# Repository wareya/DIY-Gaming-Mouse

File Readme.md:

# DIY Gaming Mouse

Video about why and how I made this, and what the various iterations were like: https://www.youtube.com/watch?v=h-Cdl4Vq9H4

This repository contains the code, schematic, PCB layout, and 3d model for a completely DIY gaming mouse, all designed around a Pixart PMW3360 sensor.

The firmware for this mouse uses a special debouncing algorithm that completely eliminates chatter without adding ANY latency, and eliminates bounce better than commercial mice do. Random double-clicks be gone!

None of the companies that make gaming mouse sensors sell them to consumers, including Pixart, so the sensor needs to be salvaged (or bought from a scalper, or a small business that specializes in reselling them).

<table>
  <tr>
    <td>
      
    </td>
    <td>
      
    </td>
  </tr>
  <tr>
    <td>
      opened mouse
    </td>
    <td>
      assembled mouse
    </td>
  </tr>
</table>

(The shell has a top, too, but it's turned off in this picture so you can see the PCB.)

## Features

- True zero-latency button debouncing with no glitching
- Buttons that will not develop double-clicking problems after only a few months
- Low-latency motion tracking (no smoothing)
- Completely open source (Apache 2.0 license)
- Even the hardware is open source! (except the processor and sensor)
- Ultra light-weight shell and assembly (55g in total)
- Fingertip-grip shell shape
- Extra middle mouse button
- - the button that normally controls DPI on other mice is mapped to M3
- PCB exposes extra unused pins from the rp2040 as test pads for hardware/firmware modding fun; attach your own sensors! or LEDs! whatever you want!
- Full 1000hz tracking

TODO:

- Configurable DPI (currently hardcoded at 1200)
- - To change it in the firmware code, edit the `spi_write(REG_CONFIG1, 11); // 1200 dpi` line, replacing 11 with your dpi divided by 100 minus 1, e.g. 7 for 800 dpi, 3 for 400, 15 for 1600, etc
- rebinding, macros, etc
- - can already be hardcoded atm if you're skilled at programming
- "fun" optional features like WMO-style diagonal jaggy removal or optional in-firmware acceleration, anti-smoothing (prediction), angle snapping, cinematic smoothing, etc
- [Wireless](https://github.com/wareya/DIY-Gaming-Mouse/issues/8)

## Required skills

You need to be familiar with, or be able to learn quickly:

- 3d printing
- how to use a "slicer" (e.g. Cura) to convert stl models to gcode (what your 3d printer uses)
- repeatedly making test prints
- how to clean up 3d prints and remove support material from fragile prints
- basic firmware code debugging skills
- the ability to read embedded C/C++ code
- the Arduino IDE (I use 2.x, not 1.x)
- desoldering (with a hot air rework station)
- soldering (with a soldering iron)
- soldering bodge wires to existing pieces of hardware without creating solder bridges (for SROM extraction)
- comfort using a hot air rework station to soften and fix misshapen parts on 3d printed objects if they print improperly
- the ability to do all of the above without wasting tons of money or burning your home down
- familiarity with PCB printing companies and PCB assembly manufacturers (JLCPCB, PCBWay, etc)
- patience

If you cannot do all of the above, you should have someone else build this project for you, rather than building it for yourself. Or, at the very least, I can't give you support if you don't have the skills needed to make this; I'm just some random guy.

You also need:

- access to a 3d printer that you can repeatedly print test prints on until they come out right
- a hot air rework station with temperature and air flow rate control
- a soldering iron with temperature control
- hot glue device (for securing the USB cable, nothing else)
- various small tools like screwdrivers, tweezers, cleanup blades / deburring tools, etc. for various parts of the building process

## Instructions

### 3D printing the shell

This assumes you're using a filament printer. Resin printers might work too, but I have never used one.

I print with PLA filament.

Print each of the STL files in the "Case Model" directory in their natural (not default!) orientations. To repeat, some of the models have to be rotated; they're saved in the orientation they have in the mouse, not the orientation they need to have on the 3d printer's build plate.

You need to convert the stl files to gcode yourself and run various test prints because each 3d printer and filament has different requirements for layer thickness, support cutoff angle, printing speed, z seam alignment placement, etc.

Cura will complain about certain pieces (like the shell bottom) not being "water tight", but it's wrong; the watertightness check doesn't handle multiple overlapping solids properly. The models will still slice correctly and without glitches.

The thumb pieces must be rotated into the orientation where they do not need any supports. This means the small part of the thumb piece is facing up, and the long part of the switch clamp section is on the bottom.

The scroll wheel must be rotated so that the thick cylinder part is on the bottom and the thin pin part is on the top. It must be printed with supports; any type of support is fine. It should be printed at 100% speed or lower, not higher, until it gets to the pin, at which point you MUST reduce the printing speed as low as you can tolerate. On my printer, a Sovol SV06, I had to turn it down to 25% speed. If your printer doesn't allow you to change the speed mid-print, you have to print at the low speed for the entire print. This is important; you have to print it slowly, because otherwise, the pin will be misaligned with itself and the scroll wheel will be off-balance and hit the middle mouse button switch with different pressures depending on where it is in its spin cycle.

Print the scroll wheel brace as-is.

Print the shell bottom as-is. However, if you have a heated printbed or chamber, you need to wait for it to completely cool before removing it. If you remove the print while it's warm, the bottom will bend and the mouse won't sit flat. Even with mouse feet, the sensor will be at the wrong height if the bottom is bent.

Print the shell top with tree supports and a support cutoff angle between 60 and 70 degrees. Do not use "standard"/traditional/grid supports; they will be too difficult to remove, and you will probably damage the print trying to remove them. On my printer, a Sovol SV06, 67 degrees was just right. If you have poor print quality, you might need to reduce the cutoff angle down to something silly like 50 degrees. If you have to go below 50 degrees, get a better printer, or make sure you're using the right filament at the right temperature, etc.

Once the shell top is printed, you need to use a deburring tool (or other hard, sharp metal implement) to remove a small amount of material from a certain curved edge along the seam where it meets the shell bottom, on the right side of the shell (with the button pieces away from you and the "butt" part towards you). The shell will fit together without removing a small amount of material from this part of the shell top, but it'll be misaligned by around a quarter of a millimeter and the right click won't quite work right. This material has to be removed because it sags during printing, and it sags during printing because of how support bridging works; the 3d model itself is correct.

You should print each part one-by-one and check for errors each time.

The final result will be somewhat rough and rugged, but it's a functional mouse shell.

### SROM preparation

Note: The SROM is optional, but highly recommended because it contains sensor firmware bugfixes. If you can't get it, comment out the call to `srom_upload();` in `pmw3360_boot()`, and then rename the `.h` file inclusion to `#include "srom_dummy_blank.h"`, but be warned that your mouse might experience glitchy behavior like "spinout" or have generally poor tracking. For example, while writing this and testing the firmware without an SROM, I click-and-dragged a title bar on a window, and then the mouse cursor teleported 300~400 pixels to the right for no reason.

The SROM needs to be captured from an existing mouse because it's copyrighted. Give it the name `srom_3360_0x03.h`, `srom_3360_0x04.h`, or `srom_3360_0x05.h`, depending on what version it is. I poked around github and found other projects using the 3360 SROM, and this seems to be the way they decided to name their SROM header files, so I'm copying the filename from them.

Once you have the SROM, edit the `#include "srom_3360_0x05.h"` line in `3360_Mouse_pico.ino` to point to the file for your SROM.

The below is instructions on how to capture the SROM from a commercial mouse.

Capture the SROM from a commercial 3360 mouse with this code, and a standalone raspberry pi pico (not this mouse's custom PCB): https://gist.github.com/wareya/0dc3498bd80be93c47b6f79aa9164321

Note: the above SROM capturing code requires you to use the "arduino-pico" board type in the Arduino IDE. But the firmware in this repostory requires you to use the "mbed OS" rp2040 board type.

Use a breadboard to make a ripping setup equivalent to that depicted in the following image:

And this post: https://github.com/wareya/DIY-Gaming-Mouse/issues/6#issuecomment-2340009477

Be very careful not to create any solder bridges between any of the pins on the 3360.

Reconnect the mouse so that it reboots and sends the SROM to the sensor again.

The output should be exactly 4094 bytes long, and the second byte should be 0x03, 0x04, or 0x05 (different versions).

Repeat the capturing process until you get the same SROM several times, just to make sure that it captured properly. To capture the SROM again, you need to reboot the mouse. This can be plugging it in to your computer again, or disconnecting and reconnecting its USB power wire, or any safe method you prefer.

The MD5 checksums of the versions of the SROM that I know about are:

```
0x03 - C64F2BDA742DD1623D6A5DC869FC5E60
0x04 - 0BCB410858FF21D091DDC497D19BC943
0x05 - 337254C54AD82C689D4B9A58D06A3CF6
```

If you have an SROM with a different version number, it might not work with this firmware. It might, but it also might not. I can't provide support for other SROM versions.

After capturing the SROM data, save it in a formatted .h file formatted as such:

```c

#define SROM_LENGTH (4094)

const uint8_t PROGMEM srom[SROM_LENGTH] =
{
0x01,
0x<version number>,
// ...
// etc
};
```

I cannot distribute the SROM in this repository, because it's copyrighted proprietary code.

Disclaimer: The above steps do not bypass any copy protection, no encryption is being broken, and copyright law is not being violated by making your own backup copy of the sensor's SROM and using it on your own device. This is fully legal in reasonable countries (like the US).

### PMW 3360 sensor salvage

The Pixart PMW3360 is not sold commercially to hobbyists or small repair shops; to get one, you have to either buy an expensive breakout board, buy it from scalpers on aliexpress (or similar), or salvage it from an existing commercial mouse. This project assumes that you're salvaging it from an existing commercial mouse, after capturing the SROM from that mouse.

You need a hot air rework station, NOT a soldering iron, to desolder and salvage the 3360 safely. If you try to use a soldering iron, even with desoldering wick and/or a desoldering pump, you are VERY likely to fail to salvage it, damaging the pins or sensor internals in the process. The 3360 is somewhat sensitive to high temperatures, so you can only heat it up for a fairly short amount of time, and desoldering the ground pin with a soldering iron will get the sensor hot enough that it might start to damage it.

The 3360 sensor's lens is usually directly mounted to the sensor by melting its clear mounting pins down onto the top of the sensor's IC package.

Take the commercial mouse's PCB, scrape off (don't break off) the top melted part of the lens's mounting posts. Then, being careful not to damage anything, remove the lens from the sensor and PCB and put it somewhere safe.

Now, put the commercial mouse's PCB upside down on a non-flammable surface, in a workspace free of any flammable material. I cannot be held responsible if you start a fire in an unsafe workspace. You have been warned!

Before continuing, you might want to cover the bottom of the sensor with paper and/or tape to prevent anything from getting inside of it. If you do this, do it in a way that doesn't create a fire hazard.

Find the bottom of the sensor's pins. To each of these pins, apply a small amount of either leaded solder (if it's all you have) or low-temperature non-leaded solder paste/gel/etc (preferred) (NOT the same thing as flux!). You want to mix your solder into the existing solder on the pins because this will lower the melting temperature of the existing solder and make it easier to desolder the chip. Use a soldering iron or hot air tool at around 600F/300C to make the two types of solder mix together. Do not physically touch the PCB or pins with the hot air tool; rely only on the air itself.

Once the solder for each pin is mixed together, pass the hot air tool over each section of pins in a circular motion until the sensor eventually, finally comes loose. At this point, use any metal tool (like metal tweezers or a screw driver) to make sure the sensor fully comes out of the PCB.

Now, use a soldering iron to clean any excess remaining solder off of the pins. If the soldering iron ends up with too much solder on it, clean it off with brass/bronze wool or similar. Be warned that, at very high temperatures, brass wool is flammable. Do not use steel wool as a subtitute, as it is even more flammable.

### PCB building and assembly

Build gerber files and drill files and all the other necessary files (BOM, pick and place, etc) that your PCB manufacturer needs to print **and assemble** the PCB. Some of the components on the PCB are very, very delicate, so unless you're a genuine expert, trying to hand-solder them is doomed.

The plugin I use to manage JLCPCB part mappings is https://github.com/Bouni/kicad-jlcpcb-tools - this is the plugin that uses the `project.db` file. However, this file is just an sqlite database, so if you want to make sure you use the right parts with another manufacturer, you can open it up with any sqlite database viewer and get the LCSC part numbers and look them up individually, then find the equivalent part for your PCBA manufacturer. However, the PCB isn't designed to require you to do this; you can look up the parts individually instead (based on their values).

Once you have your PCBs, you need the following parts to manually solder to the board:

- 6 Omron D2F-01F switches (or compatible, e.g. D2FC)
- 11mm Alps-compatible scroll wheel encoder
- salvaged PMW 3360 sensor, undamaged, pins not bent
- - 3360 sensor's lens, with mounting posts still intact
- Four dupont-compatible header pins for connecting to USB cable (optional)
- spare discrete resistors in case you messed up any of the resistor values when ordering the PCB like I did

And the following additional parts for assembly:

- USB cable, ideally with dupont-compatible connectors (you can crimp them on yourself, you don't have to buy a special cable for this)
- 3d printed shell (2 parts)
- 3d printed side buttons (2 parts)
- 3d printed scroll wheel brace (1 part)
- 3d printed scroll wheel OR salvaged scroll wheel for 11mm Alps-compatible scroll wheel encoder with the right middle-mouse-button shaft thickness
- mouse feet (salvaged or custom) with approximately 0.6mm thickness (that's zero-point-six millimeters)

The mouse feet thickness is very important, within a quarter of a millimeter! Using any other thickness of mouse feet is likely to result in poor, glitchy tracking. The PMW3360 is VERY sensitive to VERY small changes in tracking distance.

Make sure you have screws the right size to screw everything together. I recommend doing a test-fit of the shell and plain PCB with screws before doing anything else. Be careful not to overtighten the side screws; doing so can cause their mounting holes to split. The PCB is held down with two screws and the case is held together with three screws. I used salvaged screws with a major diameter (outside edge of threads) of 2mm and a minor diameter of around 1.65~1.7mm, and the holes on the case were designed around these screws, but slightly different screws will still work.

Solder the dupont-compatible header pins to the PCB, or if you have a different plan to connect the PCB to USB, do that instead. Then, connect it to your computer and make sure you can program it with the Arduino IDE. If it doesn't work, try a different copy of the PCB. Don't continue until you know that the PCB and its rp2040 processor are working properly. You should also do a test-fit of the PCB inside the 3d printed shell bottom to make sure nothing went wrong in 3d printing, and that the edge cuts and drill holes on the PCB are accurate to how they were specified in the design files.

Solder each Omron switch to the board with the plungers aligned with the outline on the silkscreen illustration. Check and double check that the switches are fully flush with the board before and while you solder them; double check that they're flush after soldering the first pin.

Test fit the PCB into the shell bottom, and without screwing anything into anything else, attach the top half of the shell and make sure that the buttons can be clicked properly and aren't clicked just by attaching the top half of the shell. If they're hard to click or they click themselves, your 3d printer has poor tolerances, and you may need to adjust the button pieces by softening them with the hot air tool and bending them slightly until they fit just right. Once you're done here, remove the PCB from the shell.

Solder the scroll wheel encoder in into the RotaryEncoder footprint on the PCB. Be very sure that it's all the way down before and while soldering it. You may need to twist the pins very slightly with a pair of needle-nose pliers to get them to fit into their holes; the holes are very narrow, on purpose, to reduce the chance of solder bridges forming between them.

(Example photo of a 11mm Alps-compatible encoder. 11mm is the distance between the center of the rotor and the surface of the PCB, not the top to bottom of the entire encoder.)

Solder the PMW3360 sensor to the center of the PCB, making VERY, VERY sure that it's in ALL THE WAY before and while soldering it. If it's not in all the way, the PCB may not fit properly in the shell, and/or the sensor may fail to track properly. The sensor must be mounted "upside-down" relative to the rest of the board, such that the text on it is upside-down compared to the text at the top of the board. If you put the sensor in the wrong way, it will look uncentered; if you put it in the right way (upside-down), it will look centered. If you get the wrong, the sensor might fry itself when you turn the mouse on, and the lens might not even fit against the sensor through the PCB.

Attach the lens to the sensor on the underside of the PCB. Then, slot the PCB into the bottom shell and make sure it fully fits all the way down.

If, at this point, you connect the mouse to USB again and check what it says in the Arduino IDE's "Serial Logger" when the mouse boots, and the SROM's ID is a value other than zero or 0xFF, the sensor is working properly. If it's working properly but still doesn't track, double check the value of the LED resistor; that's the component closest to the "U10" silkscreen text, also near four diodes arranged in a rectangle (not in a row). The resistor value should be 39 ohms, or something very close like 40. If the resistor value is wrong, you have to desolder it and bodge on 40 ohms worth of discrete resistors (I personally use two 20 ohm resistors in series). WARNING: Using too few ohms will permanently damage the sensor's LED and make the sensor useless.

Remove the PCB and fit the side button thumb pieces to their switches. This is difficult and should feel like you're almost going to break the thumb pieces, but not like you're definitely going to break them. The long piece of the switch brace should wrap around the "inside" of the switches (towards the other side button switch), not the "outside". To get the thumb pieces around the switches, first fit the "hook" to the bottom around the edge of the PCB, slightly offset from the switch, and rotate the thumb piece down so that the far end of its brace hits the top of the switch. Move it as far from the switch as you comfortably can, so that it doesn't have to bend too much to slide down past the top and around the other side of the switch. Once that happens, slide it towards the switch so that the small hook piece at the end of the brace fully wraps around the other corner of the switch. Repeat this for the other switch's thumb piece.

Above is a visual image series depicting the process for mounting the thumb button pieces. It's OK if they crack or break while attempting to fit them; they will still fit and work, just be slightly less snug than they're supposed to be.

Fit scroll wheel brace around the middle mouse button (near the right mouse button), with the spikes towards the "inside" of the mouse and away from the middle mouse button. Now fit the scroll wheel and make sure it's snug and properly balanced. If it's not, you'll need to reprint it.

Put the PCB back into the shell bottom and make sure it's still snug. Route the USB cable behind the support post in the back of the case (it has a screw hole in it) and around the right side of the PCB (NOT the left side), hugging the right side of the right mouse button, and then feed it out through the slot in the front. Use hot glue to secure the USB cable to that front slot. Make sure that it points relatively straight out the front when you hot glue it down.

Plug it in, compile and upload the firmware from the Arduino IDE, and make sure everything works. If it does, you're done! Just re-screw everything together. Be careful not to overtighten the side screws; doing so can cause their mounting holes to split.

## License

3360_Mouse_pico.ino, the main file of this project, is released under the Apache License, version 2.0.

relmouse_16.h is based on files from mbed OS, also licensed under the Apache License, version 2.0. https://github.com/arduino/ArduinoCore-mbed

The hardware design files (under "Case Model" and "KiCad schematic + PCB") are licensed under the SolderpadLicense, version 2.1, as follows:

```
Copyright 2024 wareya
SPDX-License-Identifier: Apache-2.0 WITH SHL-2.1

Licensed under the Solderpad Hardware License v 2.1 (the “License”); you may not use this file except in compliance with the License, or, at your option, the Apache License version 2.0. You may obtain a copy of the License at

https://solderpad.org/licenses/SHL-2.1/

Unless required by applicable law or agreed to in writing, any work distributed under the License is distributed on an “AS IS” BASIS, WITHOUT WARRANTIES OR CONDITIONS OF ANY KIND, either express or implied. See the License for the specific language governing permissions and limitations under the License.
```

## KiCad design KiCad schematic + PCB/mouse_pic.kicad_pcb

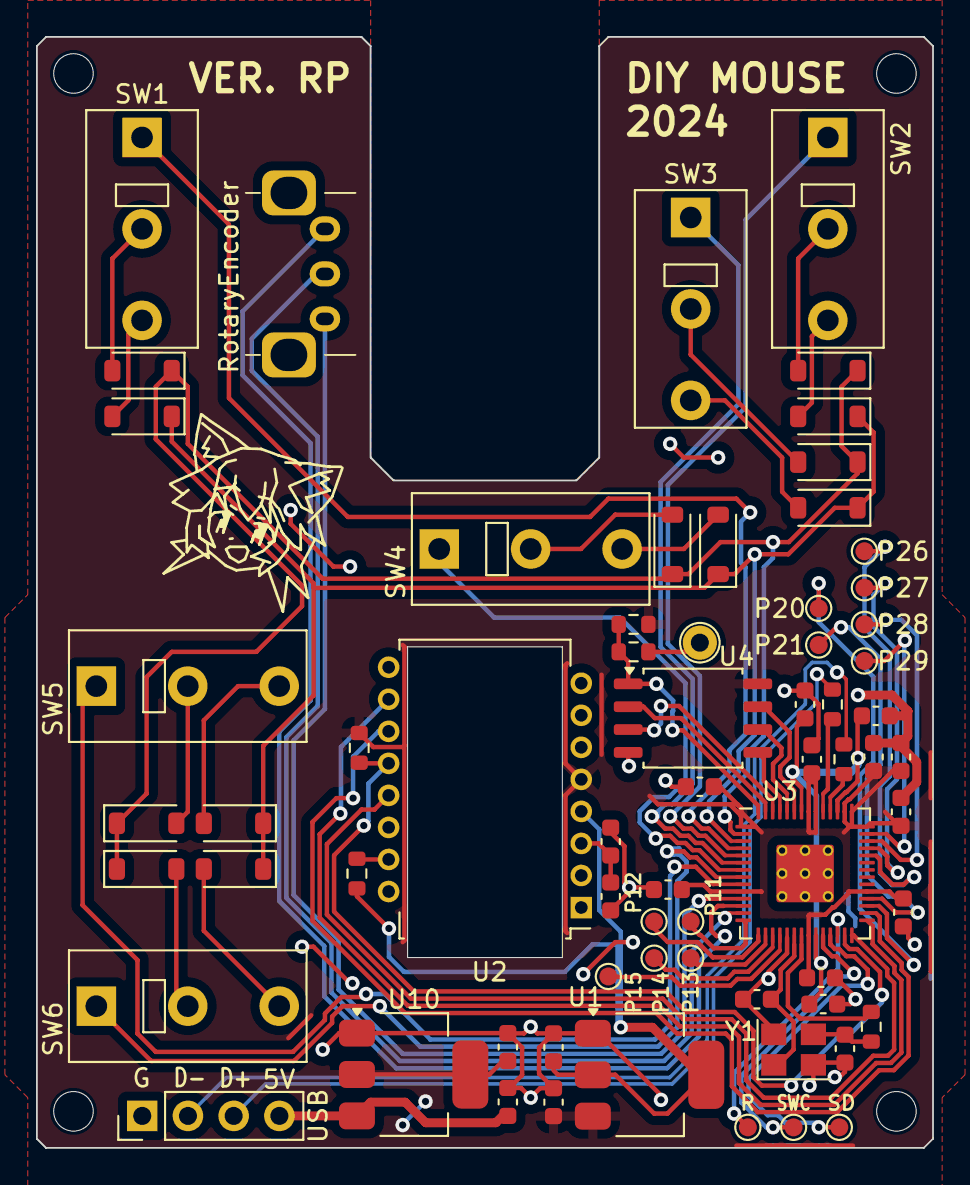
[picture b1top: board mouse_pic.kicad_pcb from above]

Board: 2 copper layers, 49.8 x 61.7 mm, 67 parts (0 on the bottom side), 62 nets.

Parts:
C1, C2: 10uF; C_0603_1608Metric
C3: 100nF; C_0603_1608Metric
C4: 4.7uF; C_0603_1608Metric
C6, C7, C9, C11, C12, C13, C14, C15, C500: 100n; C_0603_1608Metric
C8, C10: 1u; C_0603_1608Metric
C100, C400: 10u; C_0603_1608Metric
C200, C300: 15p; C_0603_1608Metric
D1, D2, D3, D4, D5, D6, D7, D8, D9, D10, D11, D12: D; D_SOD-123
Encoder1: RotaryEncoder; Alps-EC10E1220501
P11, P12, P13, P14, P15, P20, P21, P26, P27, P28, P29, P30, P31, P32: TestPoint; TestPoint_Pad_D1.0mm
R1: 10K; R_0603_1608Metric
R3, R4: 27; R_0603_1608Metric
R40: R39; R_0603_1608Metric
R100, R500: 1k; R_0603_1608Metric
R200: 10k; R_0603_1608Metric
SW1, SW2, SW3, SW4, SW5, SW6: SW_SPDT; SW_Tactile_SPDT_Omron_D2F
U1: LM1117-1.8V; SOT-223-3_TabPin2
U2: PMW3360DM-T2QU; PixArt_PDIP-16_10.9x16.2mm_P1.78mm
U3: RP2040; RP2040-QFN-56
U4: W25Q32JVSS; SOIC-8_5.275x5.275mm_P1.27mm
U10: NCP1117-3.3_SOT223; SOT-223-3_TabPin2
USB1: USB; PinHeader_1x04_P2.54mm_Vertical
USB_BOOT1: Conn_01x01_Socket; TestPoint_THTPad_D2.0mm_Drill1.0mm_Edit
Y1: ABM8-272-T3; Crystal_SMD_3225-4Pin_3.2x2.5mm

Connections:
+1V1: C6.1, C7.1, C8.1, U3.23 (DVDD), U3.45 (VREG_VOUT), U3.50 (DVDD)
+3V3: C1.1, C9.1, C10.1, C11.1, C12.1, C13.1, C14.1, C15.1, C400.1, C500.1, R1.2, R200.1, U1.3 (VI), U2.5 (VDDIO), U3.1 (IOVDD), U3.10 (IOVDD), U3.22 (IOVDD), U3.33 (IOVDD), U3.42 (IOVDD), U3.43 (ADC_AVDD), U3.44 (VREG_IN), U3.48 (USB_VDD), U3.49 (IOVDD), U4.8 (VCC), U10.2 (VO)
/3360LED: R40.1, U2.15 (LED_P)
/ENC_A: Encoder1.A, U3.11 (GPIO8)
/ENC_B: Encoder1.B, U3.13 (GPIO10)
/ENC_C: Encoder1.C, U3.12 (GPIO9)
/GPIO0: D1.1 (K), D3.1 (K), D5.1 (K), D7.1 (K), D9.1 (K), D11.1 (K), U3.2 (GPIO0)
/GPIO1: D2.1 (K), D4.1 (K), D6.1 (K), D8.1 (K), D10.1 (K), D12.1 (K), U3.3 (GPIO1)
/GPIO2: SW1.2 (B), U3.4 (GPIO2)
/GPIO3: SW2.2 (B), U3.5 (GPIO3)
/GPIO4: SW3.2 (B), U3.6 (GPIO4)
/GPIO5: SW4.2 (B), U3.7 (GPIO5)
/GPIO6: SW6.2 (B), U3.8 (GPIO6)
/GPIO7: SW5.2 (B), U3.9 (GPIO7)
/GPIO11: P11.1, U3.14 (GPIO11)
/GPIO12: P12.1, U3.15 (GPIO12)
/GPIO13: P13.1, U3.16 (GPIO13)
/GPIO14: P14.1, U3.17 (GPIO14)
/GPIO15: P15.1, U3.18 (GPIO15)
/GPIO16: R1.1, U2.12 (MISO), U3.27 (GPIO16)
/GPIO17: U2.13 (NCS), U3.28 (GPIO17)
/GPIO18: U2.10 (SCLK), U3.29 (GPIO18)
/GPIO19: U2.11 (MOSI), U3.30 (GPIO19)
/GPIO20: P20.1, U3.31 (GPIO20)
/GPIO21: P21.1, U3.32 (GPIO21)
/GPIO26_ADC0: P26.1, U3.38 (GPIO26_ADC0)
/GPIO27_ADC1: P27.1, U3.39 (GPIO27_ADC1)
/GPIO28_ADC2: P28.1, U3.40 (GPIO28_ADC2)
/GPIO29_ADC3: P29.1, U3.41 (GPIO29_ADC3)
/QSPI_SCLK: U3.52 (QSPI_SCLK), U4.6 (CLK)
/QSPI_SD0: U3.53 (QSPI_SD0), U4.5 (DI(IO0))
/QSPI_SD1: U3.55 (QSPI_SD1), U4.2 (DO(IO1))
/QSPI_SD2: U3.54 (QSPI_SD2), U4.3 (IO2)
/QSPI_SD3: U3.51 (QSPI_SD3), U4.7 (IO3)
/QSPI_SS: R100.1, R200.2, U3.56 (QSPI_SS), U4.1 (~CS)
/RUN: P30.1, U3.26 (RUN)
/SWCLK: P31.1, U3.24 (SWCLK)
/SWD: P32.1, U3.25 (SWD)
/USBD+: R3.1, USB1.3
/USBD-: R4.1, USB1.2
/V2: C2.1, R40.2, U1.2 (VO), U2.4 (VDD)
/VDDPIX: C3.1, C4.1, U2.3 (VDDPIX)
/XIN: C200.1, U3.20 (XIN), Y1.1
/XOUT: R500.1, U3.21 (XOUT)
/~USB_BOOT: R100.2, USB_BOOT1.1
GND: C1.2, C2.2, C3.2, C4.2, C6.2, C7.2, C8.2, C9.2, C10.2, C11.2, C12.2, C13.2, C14.2, C15.2, C100.2, C200.2, C300.2, C400.2, C500.2, U1.1 (GND), U2.8 (GND), U3.19 (TESTEN), U3.57 (GND), U4.4 (GND), U10.1 (GND), USB1.1, Y1.2, Y1.4
unnamed: C300.1, R500.2, Y1.3
unnamed: D1.2 (A), SW1.1 (A)
unnamed: D2.2 (A), SW1.3 (C)
unnamed: D3.2 (A), SW2.1 (A)
unnamed: D4.2 (A), SW2.3 (C)
unnamed: D5.2 (A), SW3.1 (A)
unnamed: D6.2 (A), SW3.3 (C)
unnamed: D7.2 (A), SW4.1 (A)
unnamed: D8.2 (A), SW4.3 (C)
unnamed: D9.2 (A), SW5.1 (A)
unnamed: D10.2 (A), SW5.3 (C)
unnamed: D11.2 (A), SW6.1 (A)
unnamed: D12.2 (A), SW6.3 (C)
unnamed: R4.2, U3.46 (USB_DM)
unnamed: R3.2, U3.47 (USB_DP)
VBUS: C100.1, U10.3 (VI), USB1.4

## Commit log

2024-04-07 finish readme
2024-04-07 add license
2024-04-07 specify this so it doesn't look weird
2024-04-07 clarify where I got the header file names from
2024-04-07 clarification
2024-04-07 fix grammar
2024-04-07 fix wording mistake
2024-04-07 missing part
2024-04-07 add dummy (blank) srom file for use without an srom
2024-04-07 specify license of hardware design files
2024-04-08 update scroll wheel model to fit better in the encoder
2024-04-09 change wheel updates to hardcoded checkpoints in main loop instead of interrupt timer; might improve stability (I hope)
2024-04-09 implement state latch
2024-11-24 fix bug where a stuck m3 or dpi button would block the other from working
2024-11-24 disable tracking if sensor is disconnected
2024-12-08 Update Readme.md: add Wireless plans
